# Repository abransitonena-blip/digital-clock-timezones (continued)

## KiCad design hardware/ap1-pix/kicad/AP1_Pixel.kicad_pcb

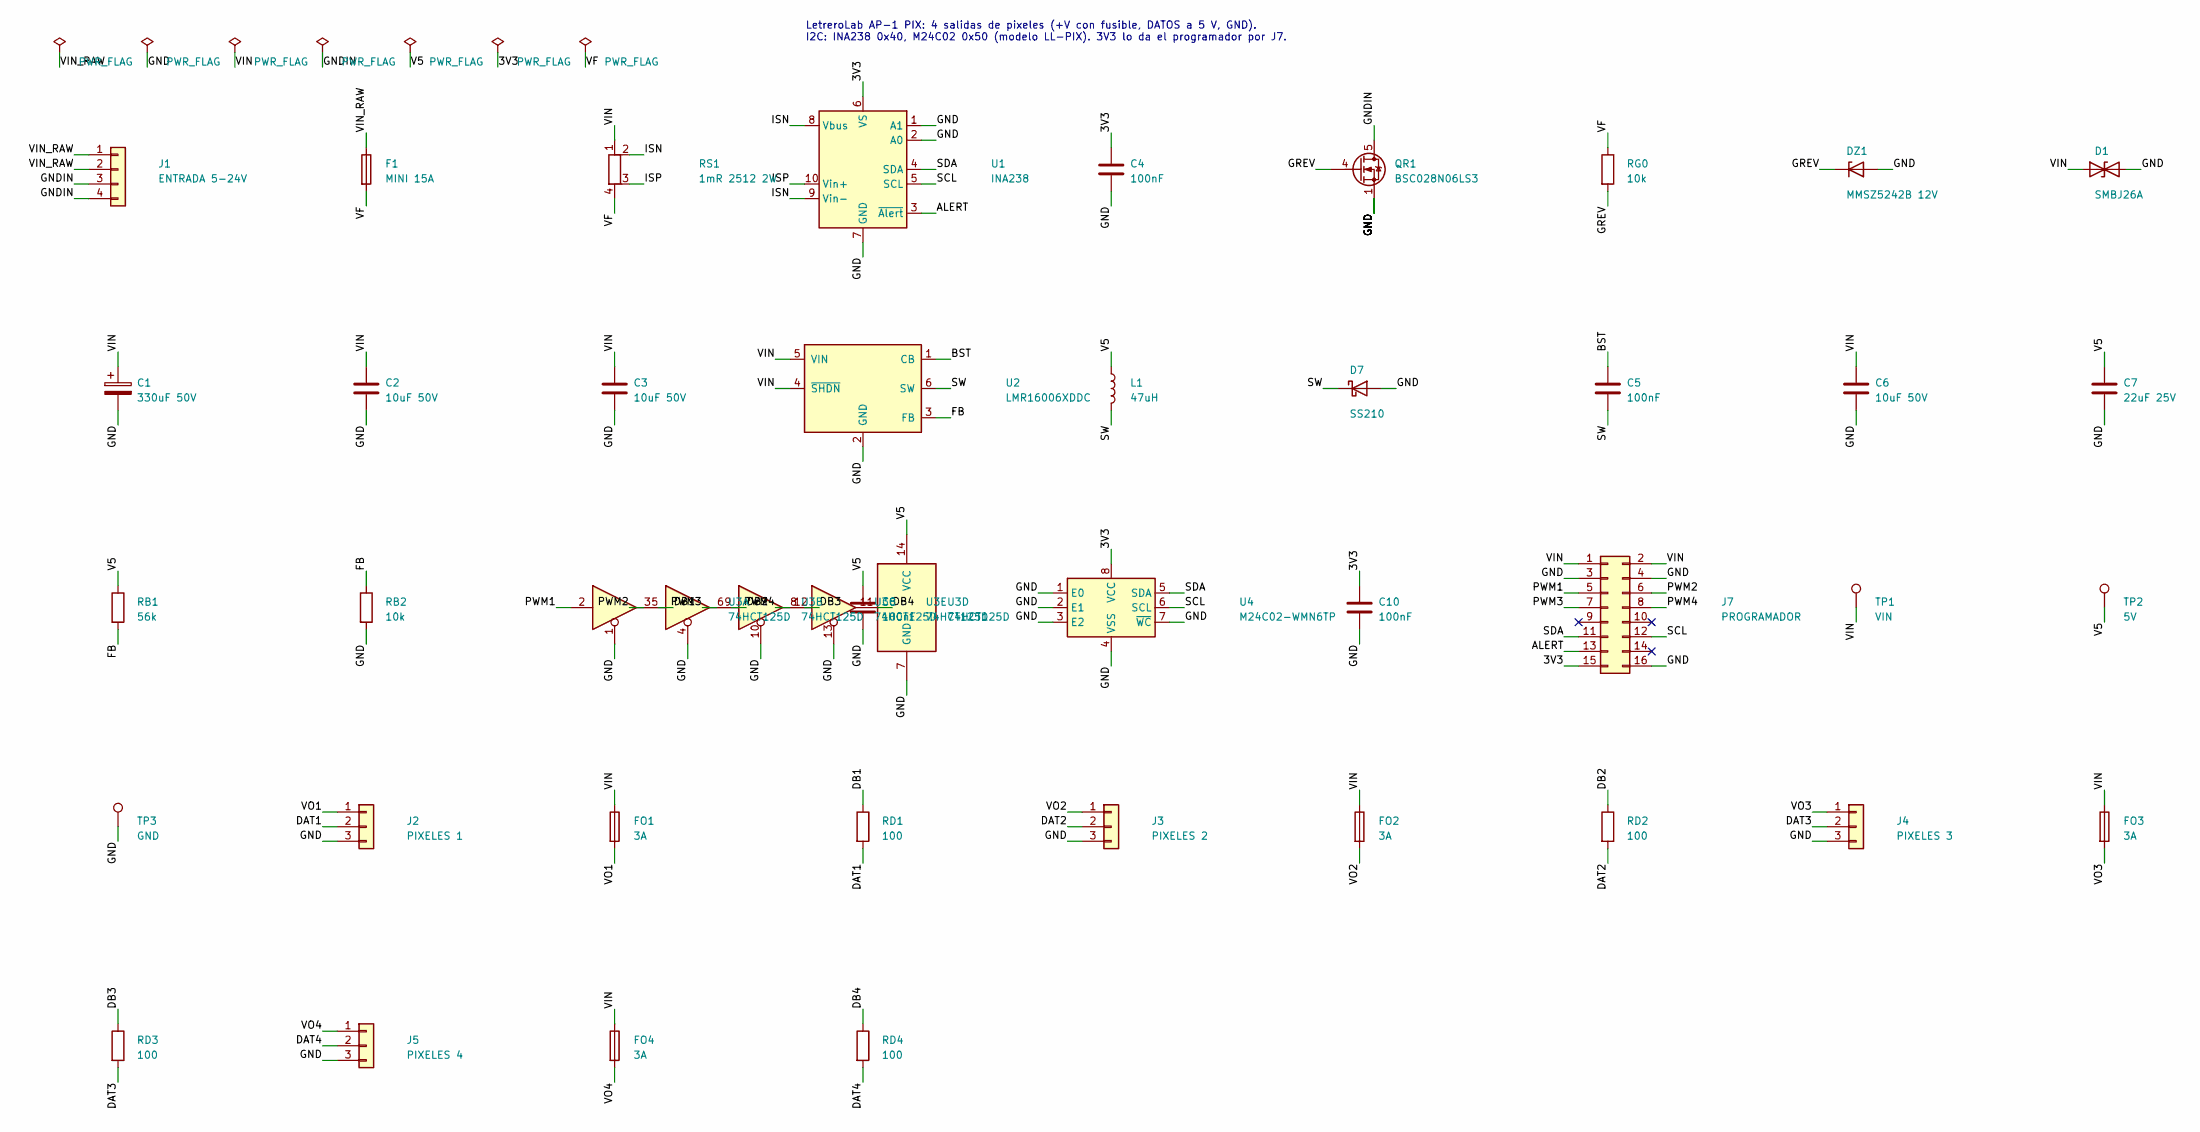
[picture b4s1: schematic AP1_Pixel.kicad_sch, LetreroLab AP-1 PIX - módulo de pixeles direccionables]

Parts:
C1: 330uF 50V; CP_Elec_10x10.5
C2, C3, C6: 10uF 50V; C_1206_3216Metric
C4, C5, C8, C10: 100nF; C_0603_1608Metric
C7: 22uF 25V; C_1206_3216Metric
D1: SMBJ26A; D_SMB
D7: SS210; D_SMA
DZ1: MMSZ5242B 12V; D_SOD-123
F1: MINI 15A; Fuseholder_Blade_Mini_Keystone_3568
FO1, FO2, FO3, FO4: 3A; Fuse_1206_3216Metric
J1: ENTRADA 5-24V; JST_VH_B4P-VH_1x04_P3.96mm_Vertical
J2: PIXELES 1; JST_VH_B3P-VH_1x03_P3.96mm_Vertical
J3: PIXELES 2; JST_VH_B3P-VH_1x03_P3.96mm_Vertical
J4: PIXELES 3; JST_VH_B3P-VH_1x03_P3.96mm_Vertical
J5: PIXELES 4; JST_VH_B3P-VH_1x03_P3.96mm_Vertical
J7: PROGRAMADOR; PinSocket_2x08_P2.54mm_Vertical
L1: 47uH; L_Changjiang_FNR4030S
QR1: BSC028N06LS3; TDSON-8-1
RB1: 56k; R_0603_1608Metric
RB2: 10k; R_0603_1608Metric
RD1, RD2, RD3, RD4: 100; R_0603_1608Metric
RG0: 10k; R_0603_1608Metric
RS1: 1mR 2512 2W; R_2512_Kelvin_NetTie
TP1: VIN; TestPoint_Pad_D1.5mm
TP2: 5V; TestPoint_Pad_D1.5mm
TP3: GND; TestPoint_Pad_D1.5mm
U1: INA238; VSSOP-10_3x3mm_P0.5mm
U2: LMR16006XDDC; SOT-23-6
U3: 74HCT125D; SOIC-14_3.9x8.7mm_P1.27mm
U4: M24C02-WMN6TP; SOIC-8_3.9x4.9mm_P1.27mm

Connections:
/3V3: C4.1, C10.1, J7.15, U1.6 (VS), U4.8 (VCC)
/ALERT: J7.13, U1.3 (~Alert)
/BST: C5.1, U2.1 (CB)
/DAT1: J2.2, RD1.2
/DAT2: J3.2, RD2.2
/DAT3: J4.2, RD3.2
/DAT4: J5.2, RD4.2
/DB1: RD1.1, U3.3
/DB2: RD2.1, U3.6
/DB3: RD3.1, U3.8
/DB4: RD4.1, U3.11
/FB: RB1.2, RB2.1, U2.3 (FB)
/GND: C1.2, C2.2, C3.2, C4.2, C6.2, C7.2, C8.2, C10.2, D1.2 (A2), D7.2 (A), DZ1.2 (A), J2.3, J3.3, J4.3, J5.3, J7.3, J7.4, J7.16, QR1.1 (S), QR1.2 (S), QR1.3 (S), RB2.2, TP3.1, U1.1 (A1), U1.2 (A0), U1.7 (GND), U2.2 (GND), U3.1, U3.4, U3.7 (GND), U3.10, U3.13, U4.1 (E0), U4.2 (E1), U4.3 (E2), U4.4 (VSS), U4.7 (~WC)
/GNDIN: J1.3, J1.4, QR1.5 (D)
/GREV: DZ1.1 (K), QR1.4 (G), RG0.2
/ISN: RS1.2, U1.8 (Vbus), U1.9 (Vin-)
/ISP: RS1.3, U1.10 (Vin+)
/PWM1: J7.5, U3.2
/PWM2: J7.6, U3.5
/PWM3: J7.7, U3.9
/PWM4: J7.8, U3.12
/SCL: J7.12, U1.5 (SCL), U4.6 (SCL)
/SDA: J7.11, U1.4 (SDA), U4.5 (SDA)
/SW: C5.2, D7.1 (K), L1.2, U2.6 (SW)
/V5: C7.1, C8.1, L1.1, RB1.1, TP2.1, U3.14 (VCC)
/VF: F1.2, RG0.1, RS1.4
/VIN: C1.1, C2.1, C3.1, C6.1, D1.1 (A1), FO1.1, FO2.1, FO3.1, FO4.1, J7.1, J7.2, RS1.1, TP1.1, U2.4 (~SHDN), U2.5 (VIN)
/VIN_RAW: F1.1, J1.1, J1.2
/VO1: FO1.2, J2.1
/VO2: FO2.2, J3.1
/VO3: FO3.2, J4.1
/VO4: FO4.2, J5.1

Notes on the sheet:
LetreroLab AP-1 PIX: 4 salidas de pixeles (+V con fusible, DATOS a 5 V, GND). I2C: INA238 0x40, M24C02 0x50 (modelo LL-PIX). 3V3 lo da el programador por J7.

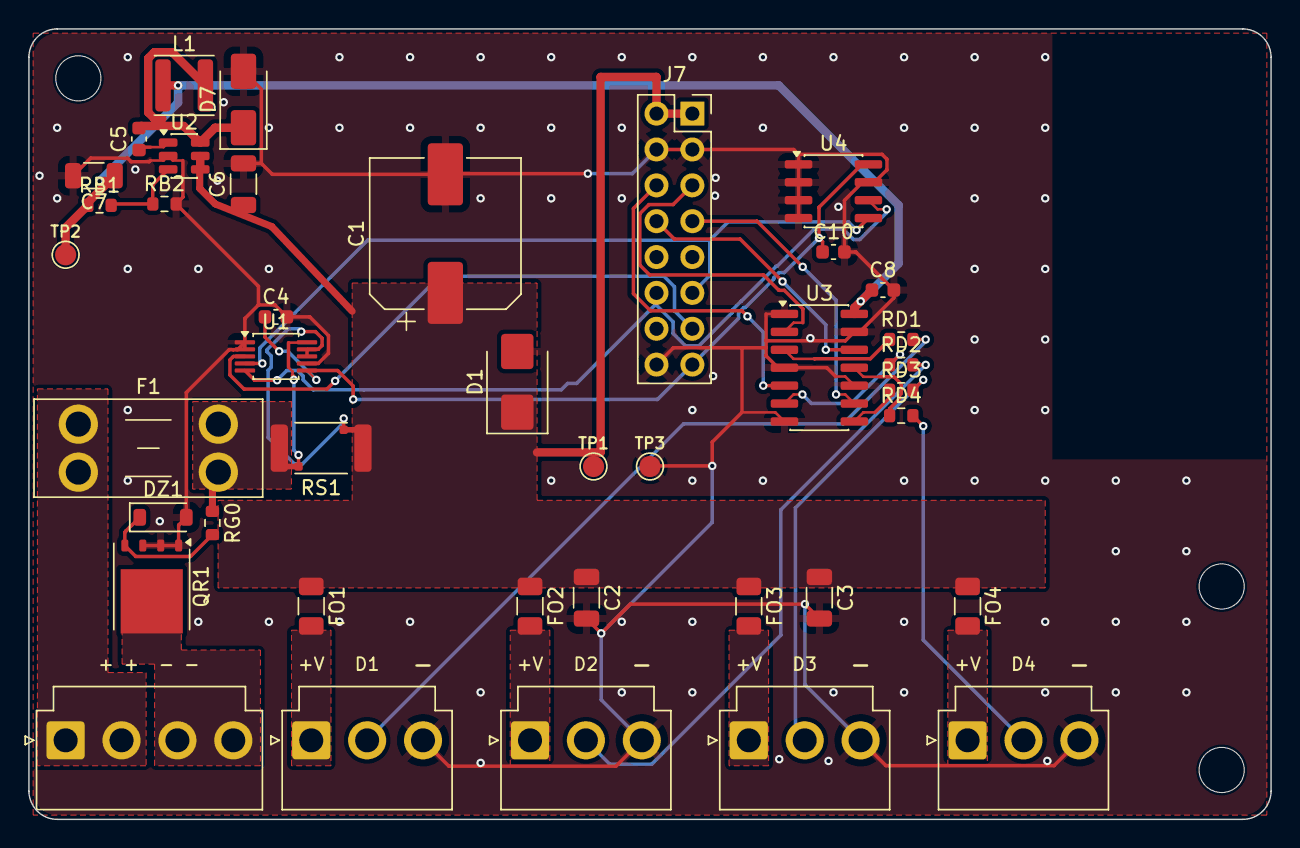
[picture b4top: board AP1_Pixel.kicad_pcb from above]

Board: 2 copper layers, 88.0 x 56.0 mm, 43 parts (0 on the bottom side), 32 nets.

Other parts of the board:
H1, H2, H3: MountingHole_3.2mm_M3

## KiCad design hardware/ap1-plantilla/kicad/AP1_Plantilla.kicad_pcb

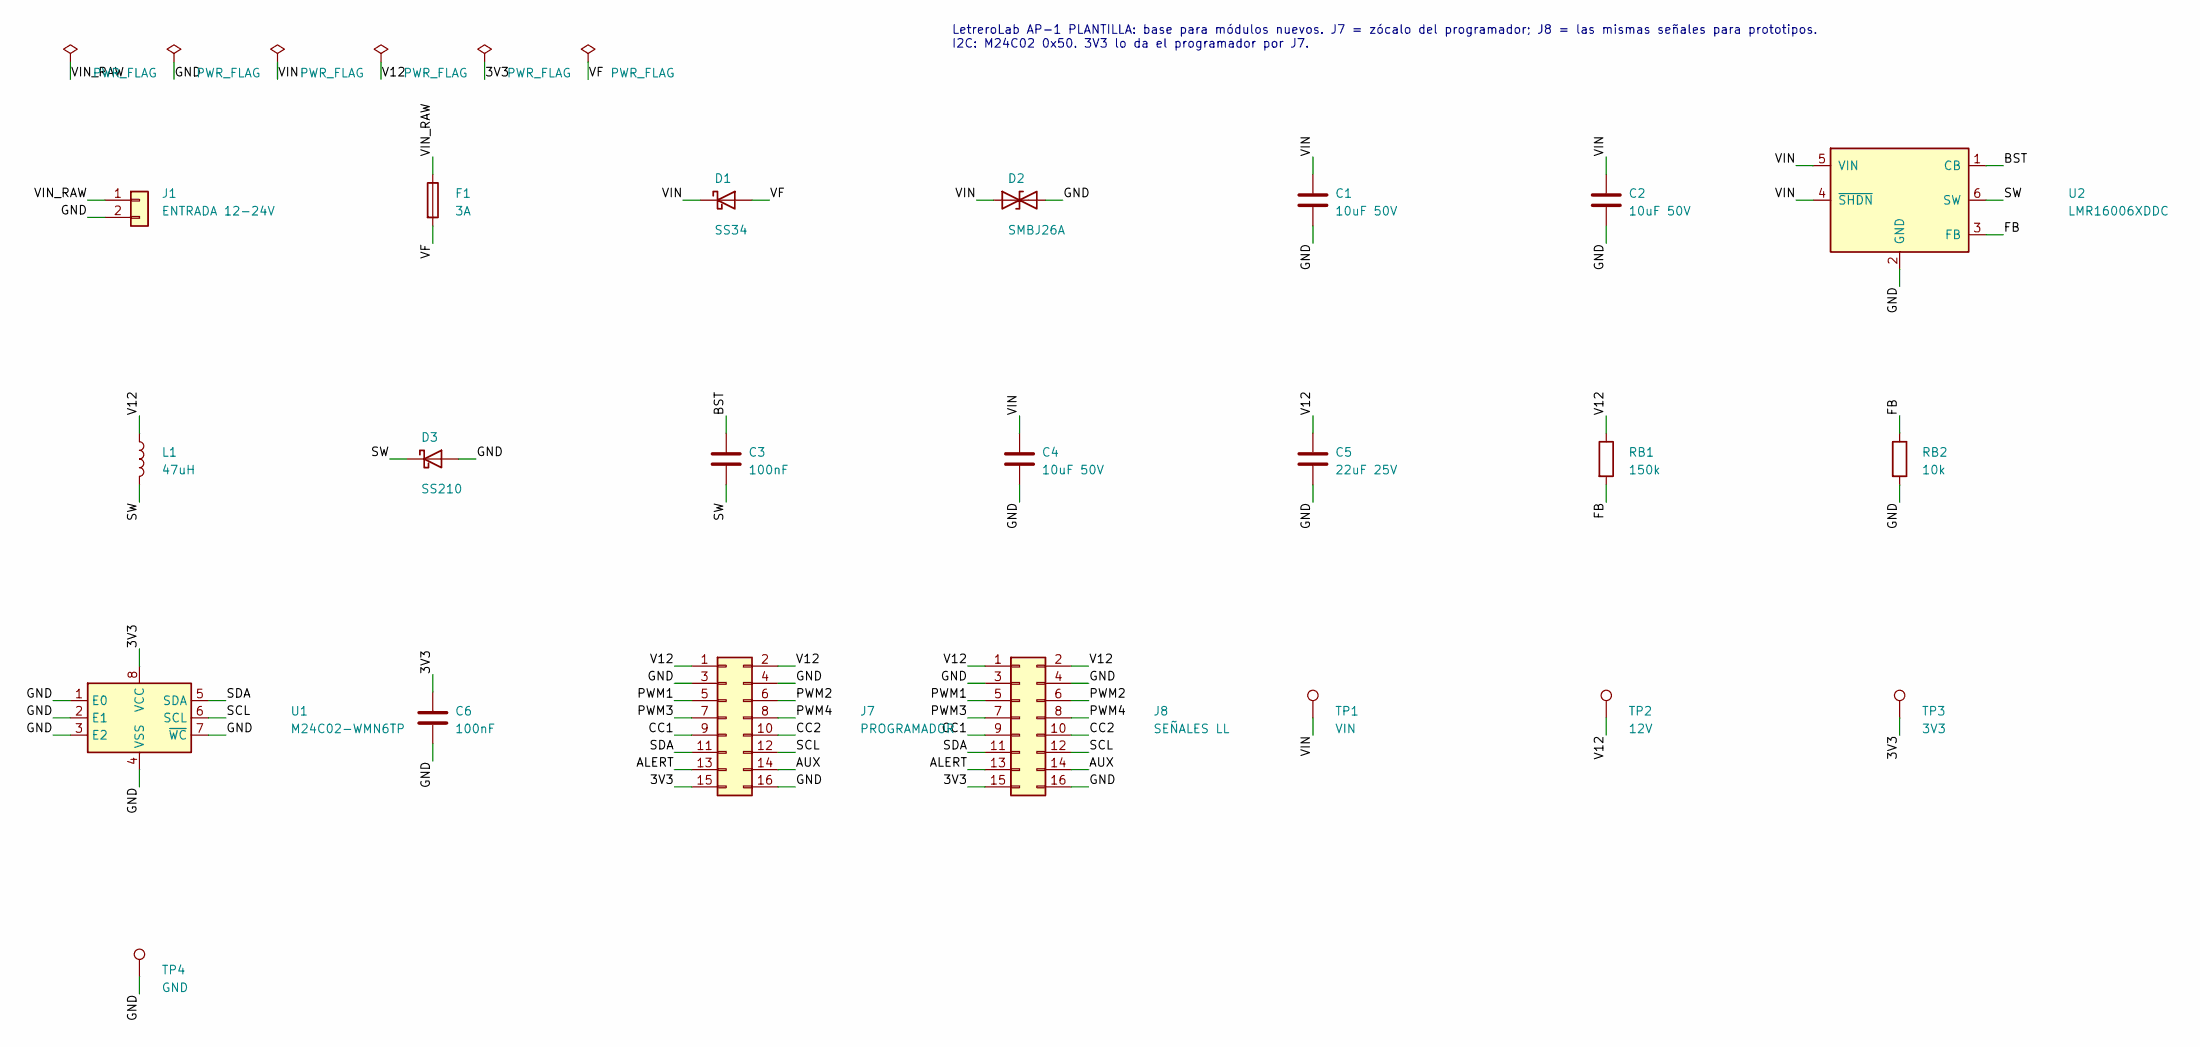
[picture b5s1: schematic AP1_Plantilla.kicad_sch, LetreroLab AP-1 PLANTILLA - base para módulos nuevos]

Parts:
C1, C2, C4: 10uF 50V; C_1206_3216Metric
C3, C6: 100nF; C_0603_1608Metric
C5: 22uF 25V; C_1206_3216Metric
D1: SS34; D_SMA
D2: SMBJ26A; D_SMB
D3: SS210; D_SMA
F1: 3A; Fuse_1206_3216Metric
J1: ENTRADA 12-24V; JST_VH_B2P-VH_1x02_P3.96mm_Vertical
J7: PROGRAMADOR; PinSocket_2x08_P2.54mm_Vertical
J8: SEÑALES LL; PinHeader_2x08_P2.54mm_Vertical
L1: 47uH; L_Changjiang_FNR4030S
RB1: 150k; R_0603_1608Metric
RB2: 10k; R_0603_1608Metric
TP1: VIN; TestPoint_Pad_D1.5mm
TP2: 12V; TestPoint_Pad_D1.5mm
TP3: 3V3; TestPoint_Pad_D1.5mm
TP4: GND; TestPoint_Pad_D1.5mm
U1: M24C02-WMN6TP; SOIC-8_3.9x4.9mm_P1.27mm
U2: LMR16006XDDC; SOT-23-6

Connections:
/3V3: C6.1, J7.15, J8.15, TP3.1, U1.8 (VCC)
/ALERT: J7.13, J8.13
/AUX: J7.14, J8.14
/BST: C3.1, U2.1 (CB)
/CC1: J7.9, J8.9
/CC2: J7.10, J8.10
/FB: RB1.2, RB2.1, U2.3 (FB)
/GND: C1.2, C2.2, C4.2, C5.2, C6.2, D2.2 (A2), D3.2 (A), J1.2, J7.3, J7.4, J7.16, J8.3, J8.4, J8.16, RB2.2, TP4.1, U1.1 (E0), U1.2 (E1), U1.3 (E2), U1.4 (VSS), U1.7 (~WC), U2.2 (GND)
/PWM1: J7.5, J8.5
/PWM2: J7.6, J8.6
/PWM3: J7.7, J8.7
/PWM4: J7.8, J8.8
/SCL: J7.12, J8.12, U1.6 (SCL)
/SDA: J7.11, J8.11, U1.5 (SDA)
/SW: C3.2, D3.1 (K), L1.2, U2.6 (SW)
/V12: C5.1, J7.1, J7.2, J8.1, J8.2, L1.1, RB1.1, TP2.1
/VF: D1.2 (A), F1.2
/VIN: C1.1, C2.1, C4.1, D1.1 (K), D2.1 (A1), TP1.1, U2.4 (~SHDN), U2.5 (VIN)
/VIN_RAW: F1.1, J1.1

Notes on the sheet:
LetreroLab AP-1 PLANTILLA: base para módulos nuevos. J7 = zócalo del programador; J8 = las mismas señales para prototipos. I2C: M24C02 0x50. 3V3 lo da el programador por J7.

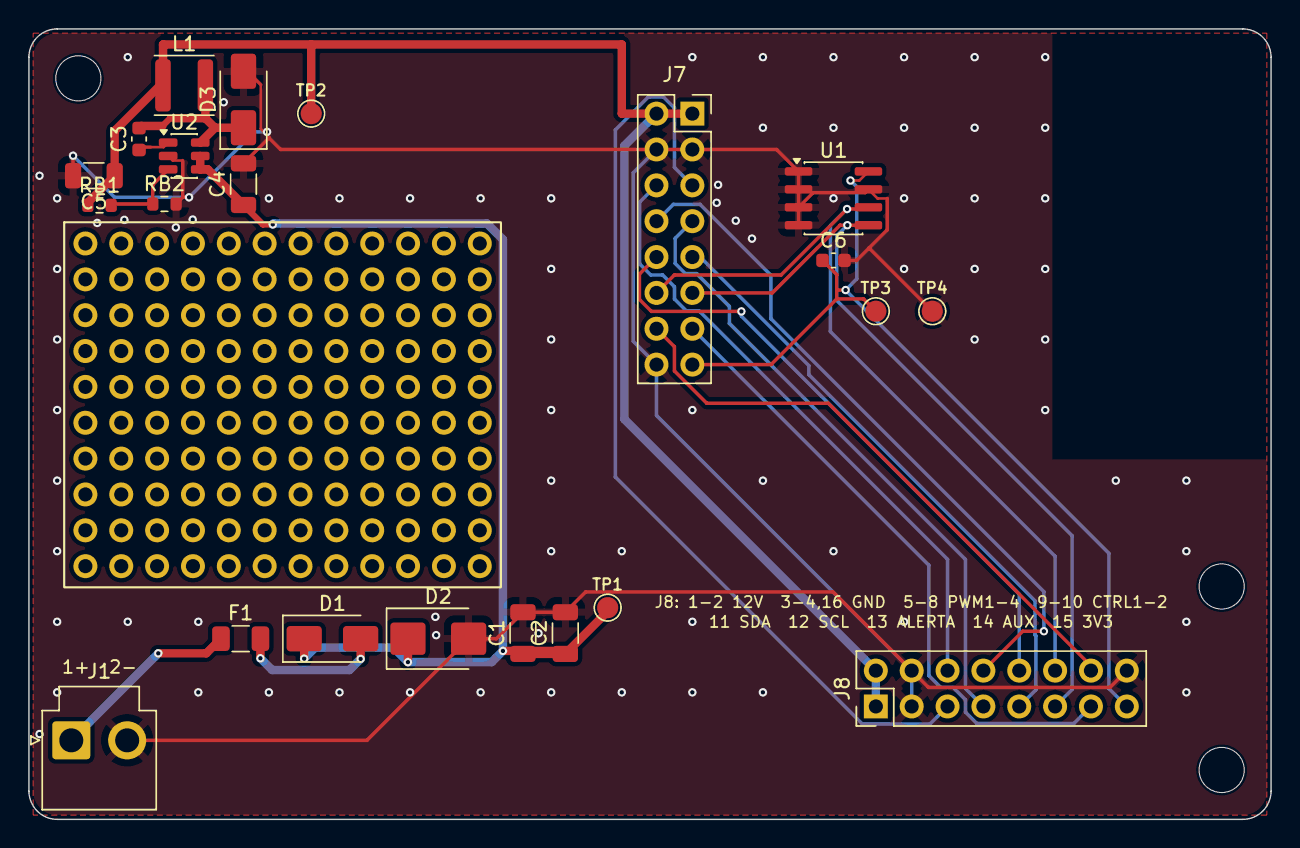
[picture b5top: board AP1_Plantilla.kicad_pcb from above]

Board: 2 copper layers, 88.0 x 56.0 mm, 26 parts (0 on the bottom side), 19 nets.

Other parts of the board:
H1, H2, H3: MountingHole_3.2mm_M3
PROTO1: Prototipo; Prototipo_2.54mm_12x10

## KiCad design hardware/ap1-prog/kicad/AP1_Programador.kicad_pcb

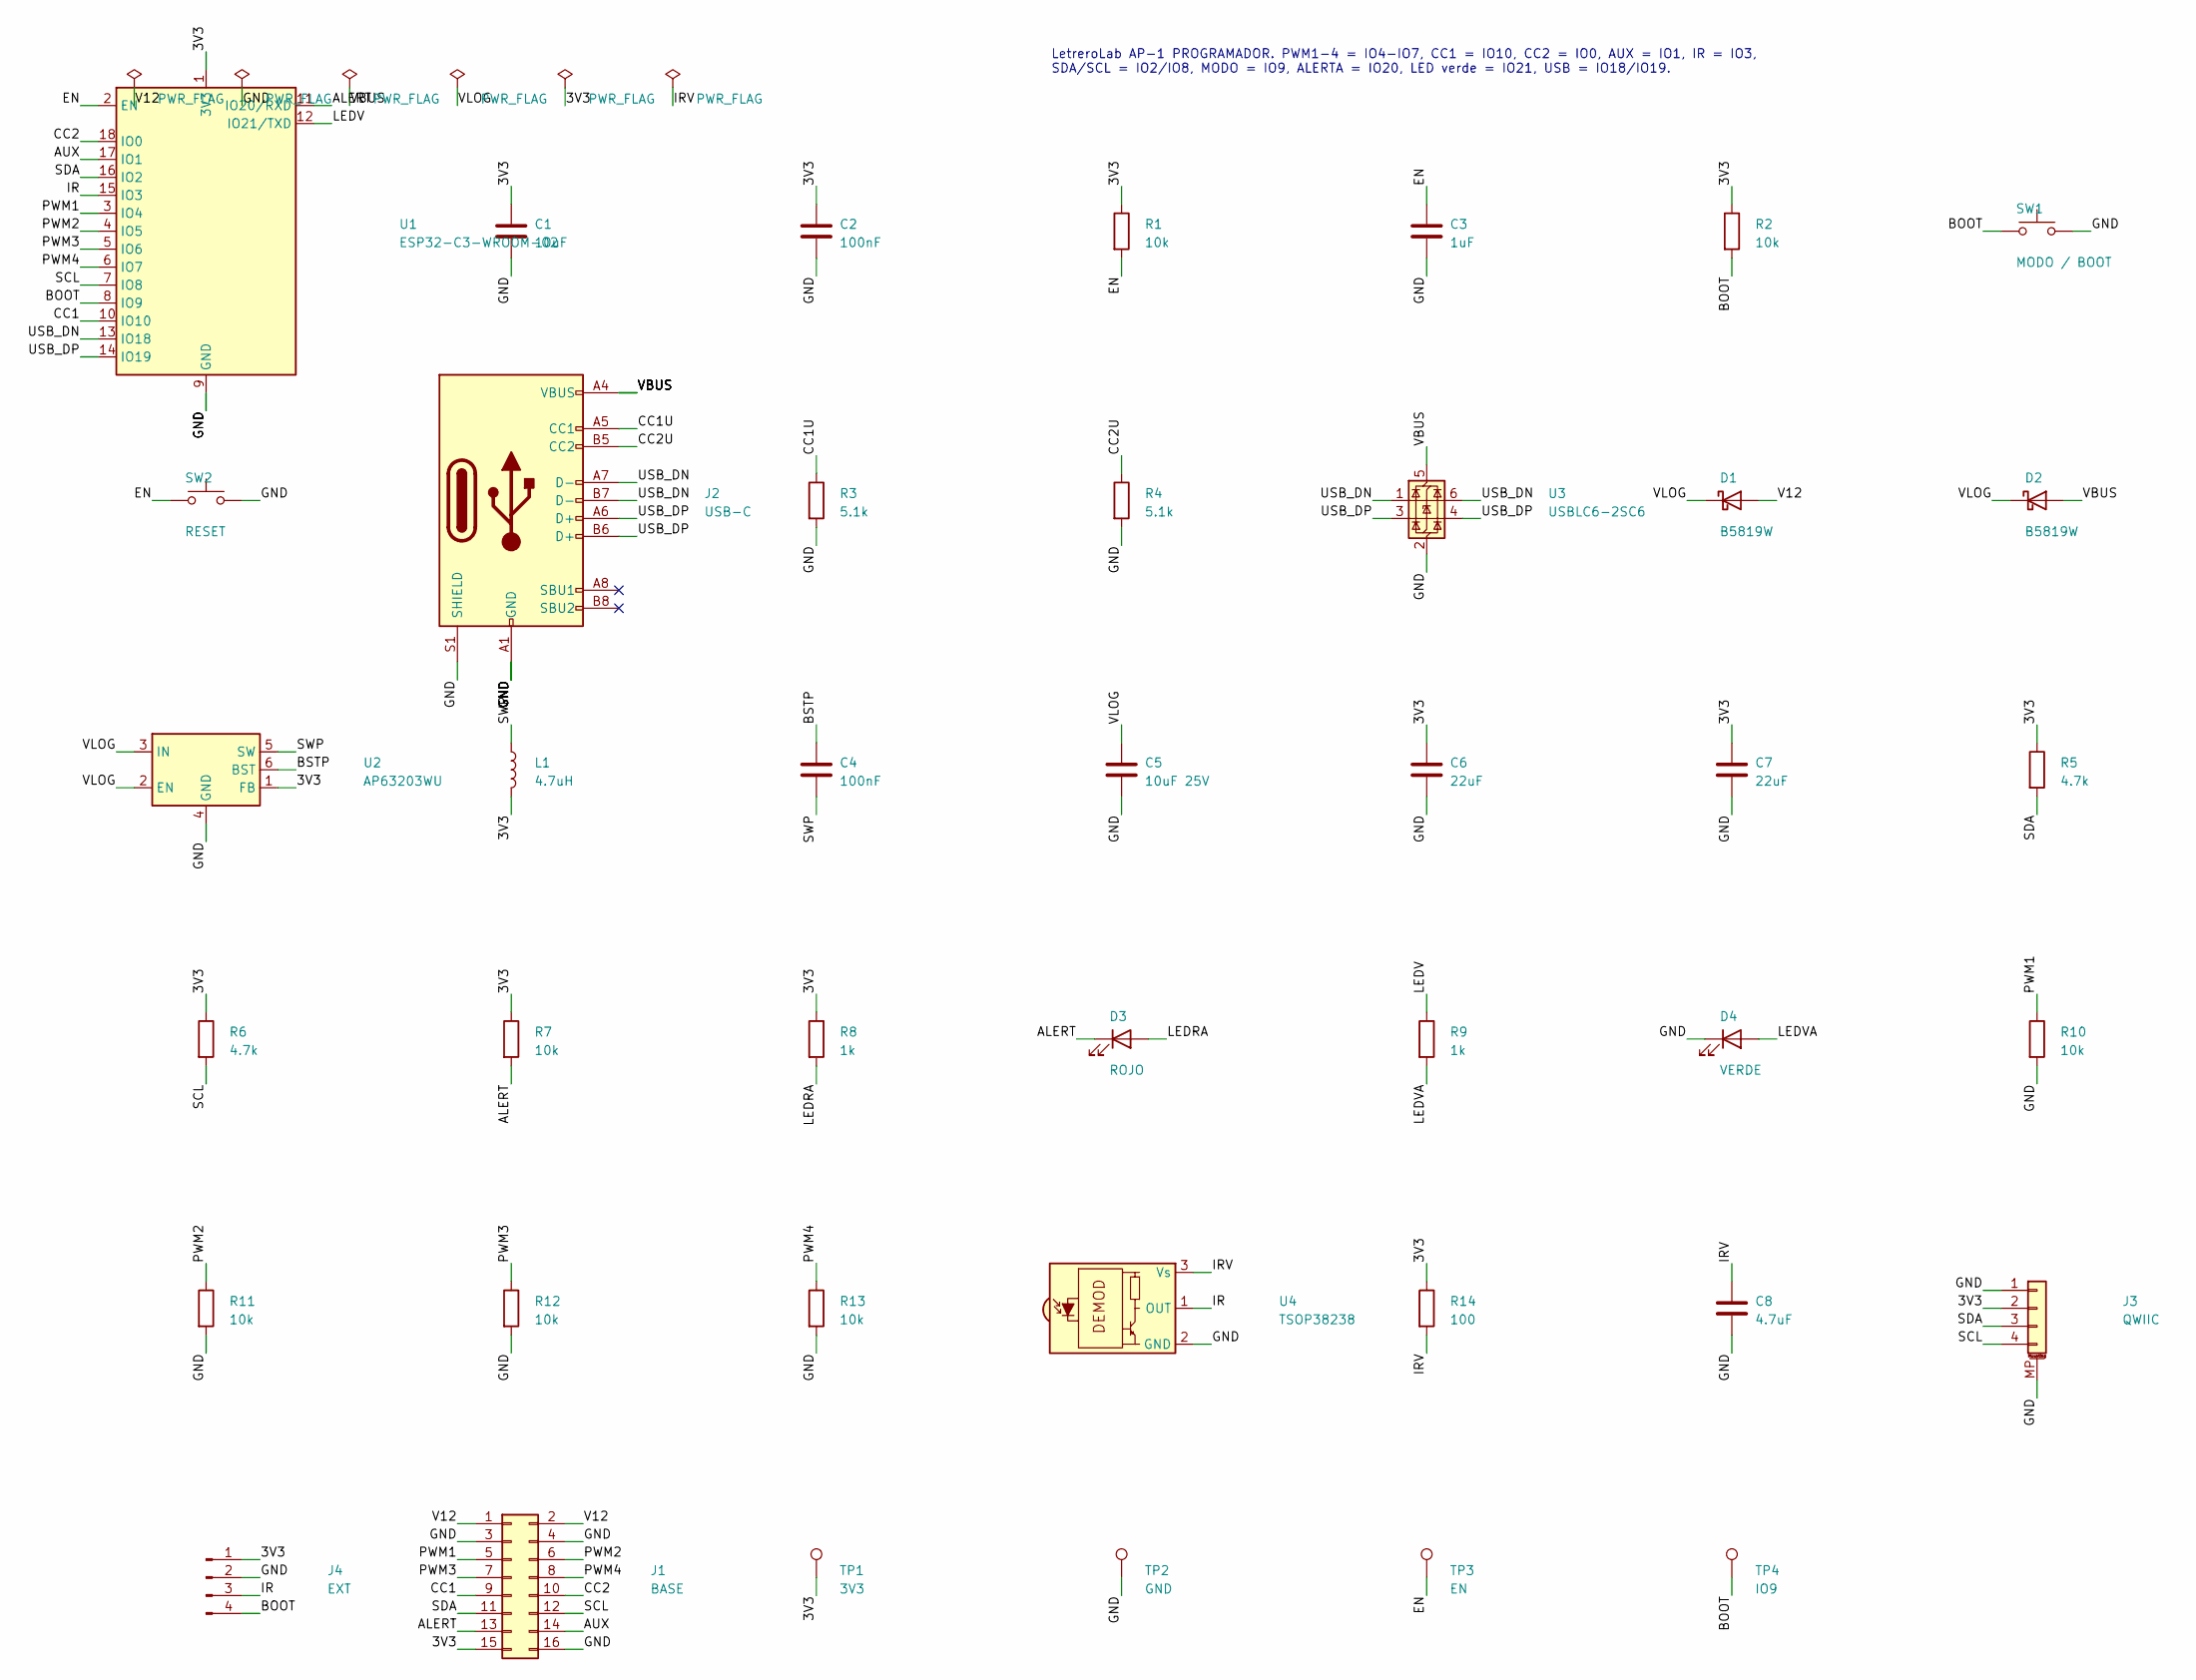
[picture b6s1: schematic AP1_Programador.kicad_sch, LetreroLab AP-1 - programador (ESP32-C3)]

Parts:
C1: 10uF; C_0805_2012Metric
C2, C4: 100nF; C_0603_1608Metric
C3: 1uF; C_0603_1608Metric
C5: 10uF 25V; C_1206_3216Metric
C6, C7: 22uF; C_0805_2012Metric
C8: 4.7uF; C_0603_1608Metric
D1, D2: B5819W; D_SOD-123
D3: ROJO; LED_0603_1608Metric
D4: VERDE; LED_0603_1608Metric
J1: BASE; PinHeader_2x08_P2.54mm_Vertical
J2: USB-C; USB_C_Receptacle_HRO_TYPE-C-31-M-12
J3: QWIIC; JST_SH_SM04B-SRSS-TB_1x04-1MP_P1.00mm_Horizontal
J4: EXT; PinHeader_1x04_P2.54mm_Vertical
L1: 4.7uH; L_Changjiang_FNR4030S
R1, R2, R7, R10, R11, R12, R13: 10k; R_0603_1608Metric
R3, R4: 5.1k; R_0603_1608Metric
R5, R6: 4.7k; R_0603_1608Metric
R8, R9: 1k; R_0603_1608Metric
R14: 100; R_0603_1608Metric
SW1: MODO / BOOT; SW_Push_1P1T_XKB_TS-1187A
SW2: RESET; SW_Push_1P1T_XKB_TS-1187A
TP1: 3V3; TestPoint_Pad_D1.5mm
TP2: GND; TestPoint_Pad_D1.5mm
TP3: EN; TestPoint_Pad_D1.5mm
TP4: IO9; TestPoint_Pad_D1.5mm
U1: ESP32-C3-WROOM-02; ESP32-C3-WROOM-02_JLC
U2: AP63203WU; TSOT-23-6
U3: USBLC6-2SC6; SOT-23-6
U4: TSOP38238; Vishay_MINICAST-3Pin

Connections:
/3V3: C1.1, C2.1, C6.1, C7.1, J1.15, J3.2, J4.1, L1.2, R1.1, R2.1, R5.1, R6.1, R7.1, R8.1, R14.1, TP1.1, U1.1 (3V3), U2.1 (FB)
/ALERT: D3.1 (K), J1.13, R7.2, U1.11 (IO20/RXD)
/AUX: J1.14, U1.17 (IO1)
/BOOT: J4.4, R2.2, SW1.1, TP4.1, U1.8 (IO9)
/BSTP: C4.1, U2.6 (BST)
/CC1: J1.9, U1.10 (IO10)
/CC1U: J2.A5 (CC1), R3.1
/CC2: J1.10, U1.18 (IO0)
/CC2U: J2.B5 (CC2), R4.1
/EN: C3.1, R1.2, SW2.1, TP3.1, U1.2 (EN)
/GND: C1.2, C2.2, C3.2, C5.2, C6.2, C7.2, C8.2, D4.1 (K), J1.3, J1.4, J1.16, J2.A1 (GND), J2.A12 (GND), J2.B1 (GND), J2.B12 (GND), J2.S1 (SHIELD), J3.1, J3.MP (MountPin), J4.2, R3.2, R4.2, R10.2, R11.2, R12.2, R13.2, SW1.2, SW2.2, TP2.1, U1.9 (GND), U1.19 (GND), U2.4 (GND), U3.2 (GND), U4.2 (GND)
/IR: J4.3, U1.15 (IO3), U4.1 (OUT)
/IRV: C8.1, R14.2, U4.3 (Vs)
/LEDRA: D3.2 (A), R8.2
/LEDV: R9.1, U1.12 (IO21/TXD)
/LEDVA: D4.2 (A), R9.2
/PWM1: J1.5, R10.1, U1.3 (IO4)
/PWM2: J1.6, R11.1, U1.4 (IO5)
/PWM3: J1.7, R12.1, U1.5 (IO6)
/PWM4: J1.8, R13.1, U1.6 (IO7)
/SCL: J1.12, J3.4, R6.2, U1.7 (IO8)
/SDA: J1.11, J3.3, R5.2, U1.16 (IO2)
/SWP: C4.2, L1.1, U2.5 (SW)
/USB_DN: J2.A7 (D-), J2.B7 (D-), U1.13 (IO18), U3.1 (I/O1), U3.6 (I/O1)
/USB_DP: J2.A6 (D+), J2.B6 (D+), U1.14 (IO19), U3.3 (I/O2), U3.4 (I/O2)
/V12: D1.2 (A), J1.1, J1.2
/VBUS: D2.2 (A), J2.A4 (VBUS), J2.A9 (VBUS), J2.B4 (VBUS), J2.B9 (VBUS), U3.5 (VBUS)
/VLOG: C5.1, D1.1 (K), D2.1 (K), U2.2 (EN), U2.3 (IN)

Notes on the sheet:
LetreroLab AP-1 PROGRAMADOR. PWM1-4 = IO4-IO7, CC1 = IO10, CC2 = IO0, AUX = IO1, IR = IO3, SDA/SCL = IO2/IO8, MODO = IO9, ALERTA = IO20, LED verde = IO21, USB = IO18/IO19.

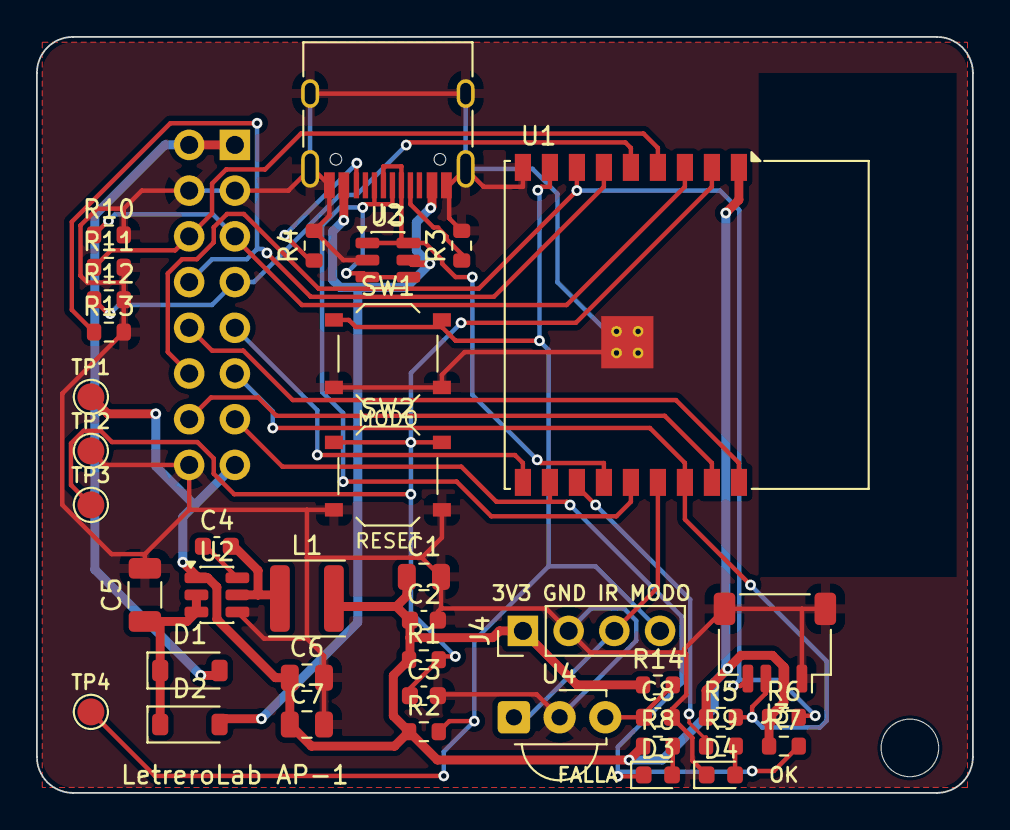
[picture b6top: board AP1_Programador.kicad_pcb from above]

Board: 2 copper layers, 52.0 x 42.0 mm, 42 parts (1 on the bottom side), 28 nets.

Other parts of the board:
H1: MountingHole_3.2mm_M3
